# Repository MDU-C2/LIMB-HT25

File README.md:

# LIMB

LIMB is a student project at [Mälardalen University](https://www.mdu.se/) with the aim of creating a bionic arm
to be used in the rehabilitation process of stroke survivors. The arm was
developed in collaboration with [Universidad de Antioquia](http://www.udea.edu.co/),
[Universidad Tecnológica de Panamá](https://utp.ac.pa/), and
[UC Berkeley](https://www.berkeley.edu/).

## Platforms used

The microcontrollers used are ESP32-C3-Zeros and the main computer is an [NVIDIA Jetson AGX Orin Developer Kit](https://www.nvidia.com/en-us/autonomous-machines/embedded-systems/jetson-orin/).

## Controlling the arm

To control the arm first connect to the NVIDIA Jetson AGX Orin. See
the [AGX Orin documentation](/docs/jetson_agx_orin.md) for more details on how to connect to it.
Then you can use CAN messages to control the arm and get information from its sensors.
See the [CAN documentation](/docs/can/can.md) for more details regarding sending and receiving
CAN messages using the AGX Orin. There are various
ready-made python scripts in the [`/src/`](/src/) directory that can be used to control the arm.
See [`/src/README.md`](/src/README.md) for more details on how to run the python scripts.

## Structure of repository

The key parts of the repository are:

- [`scripts/`](./scripts/)
  - Contains a script to set up the virtual CAN interfaces on the Orin.
- [`src/esp32/`](./src/esp32)
  - Contains the programs for the ESP32-C3-Zero modules controlling the motors and reading from the sensors on the robot arm.
- [`src/layers/`](./src/layers)
  - Contains the main program running on the AGX Orin, reading sensor values over the CAN bus from the ESP32s and over Bluetooth Low Energy from the user before figuring out how the robot arm should behave and sending out the new joint angles on the CAN bus to the ESP32s.

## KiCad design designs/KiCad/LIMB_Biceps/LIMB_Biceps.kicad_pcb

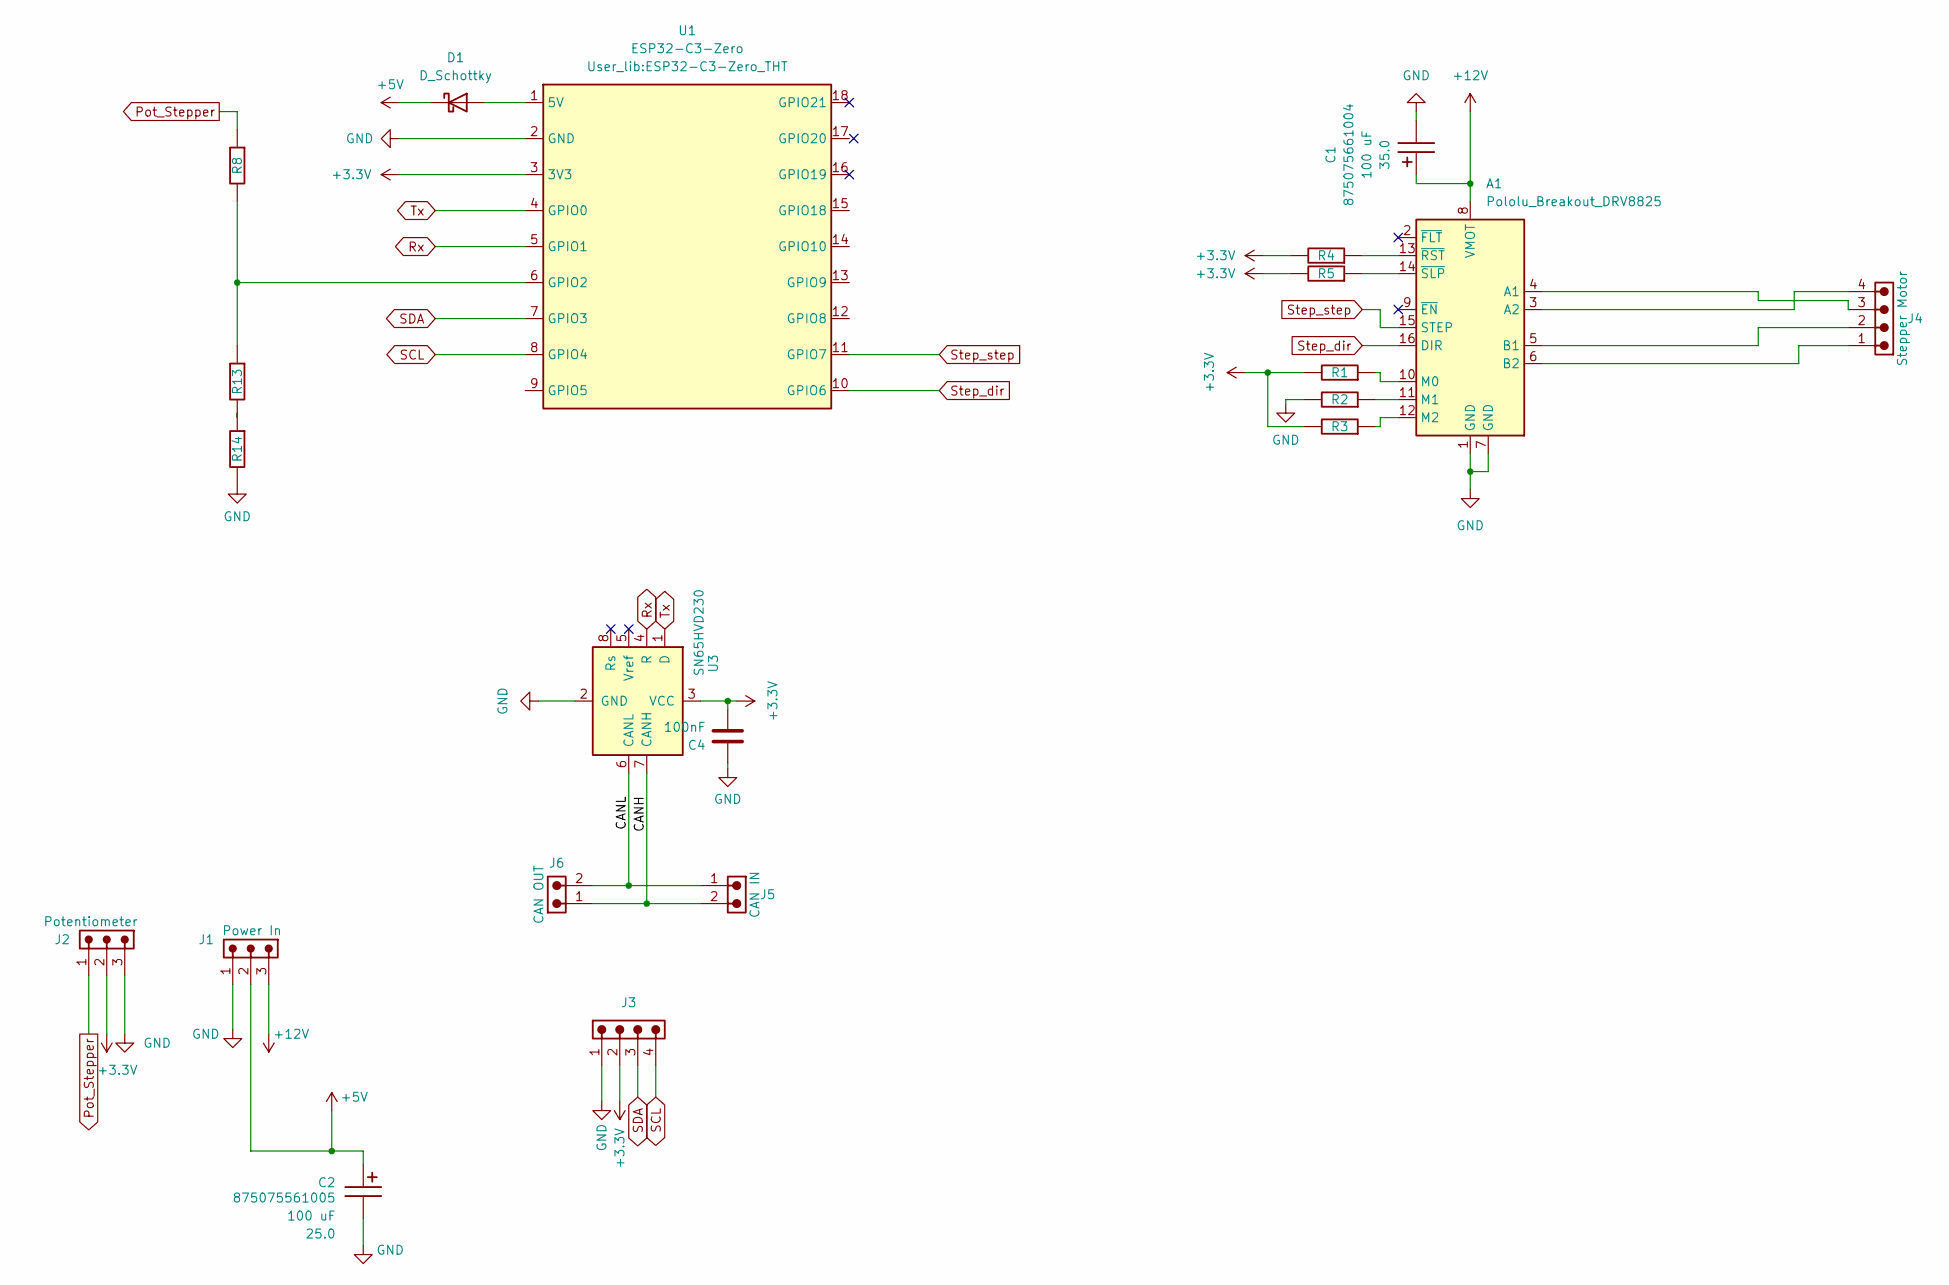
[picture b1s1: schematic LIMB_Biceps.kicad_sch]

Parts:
A1: Pololu_Breakout_DRV8825; Pololu_Breakout-16_15.2x20.3mm
C1: 100 uF; CP_Wurth_WCAP-ASLL-D6.3L5.5; Voltage 35.0; Part Number 875075661004
C2: 100 uF; CP_Wurth_WCAP-ASLL-D6.3L5.5; Voltage 25.0; Part Number 875075561005
C4: 100nF; C_0805_2012Metric_Pad1.18x1.45mm_HandSolder
D1: D_Schottky; D_SMA
J1: Power In; J_Wurth_WR-NPC2_626003110201; Part Number 626003110201
J2: Potentiometer; J_Wurth_WR-NPC2_626003110201; Part Number 626003110201
J3: IMU; J_Wurth_WR-WTB_68800411722; Working Voltage (V (AC)) 250
J4: Stepper Motor; J_Wurth_WR-WTB_68800411722; Working Voltage (V (AC)) 250
J5: CAN IN; J_Wurth_WR-WTB_68800211622; Working Voltage (V (AC)) 250
J6: CAN OUT; J_Wurth_WR-WTB_68800211622; Working Voltage (V (AC)) 250
R1, R2, R3, R4, R5, R8, R13, R14: 10K; R_0805_2012Metric
U1: ESP32-C3-Zero; ESP32-C3-Zero_THT
U3: SN65HVD230; SOIC-8_3.9x4.9mm_P1.27mm

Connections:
+3.3V: C4.2, J2.2, J3.2, R1.1, R3.1, R4.1, R5.1, U1.3 (3V3), U3.3 (VCC)
+5V: C2.1, D1.1 (K), J1.2
+12V: A1.8 (VMOT), C1.1, J1.3
/CANH: J5.2, J6.1, U3.7 (CANH)
/CANL: J5.1, J6.2, U3.6 (CANL)
GND: A1.1 (GND), A1.7 (GND), C1.2, C2.2, C4.1, J1.1, J2.3, J3.1, R2.1, R14.1, U1.2 (GND), U3.2 (GND)
unnamed: A1.4 (A1), J4.3
unnamed: A1.3 (A2), J4.4
unnamed: A1.5 (B1), J4.2
unnamed: A1.6 (B2), J4.1
unnamed: A1.10 (M0), R1.2
unnamed: A1.11 (M1), R2.2
unnamed: A1.12 (M2), R3.2
unnamed: A1.13 (~RST), R4.2
unnamed: A1.14 (~SLP), R5.2
unnamed: D1.2 (A), U1.1 (5V)
unnamed: R13.1, R14.2
unnamed: R8.1, R13.2, U1.6 (GPIO2)
Pot_Stepper: J2.1, R8.2
Rx: U1.5 (GPIO1), U3.4 (R)
SCL: J3.4, U1.8 (GPIO4)
SDA: J3.3, U1.7 (GPIO3)
Step_dir: A1.16 (DIR), U1.10 (GPIO6)
Step_step: A1.15 (STEP), U1.11 (GPIO7)
Tx: U1.4 (GPIO0), U3.1 (D)

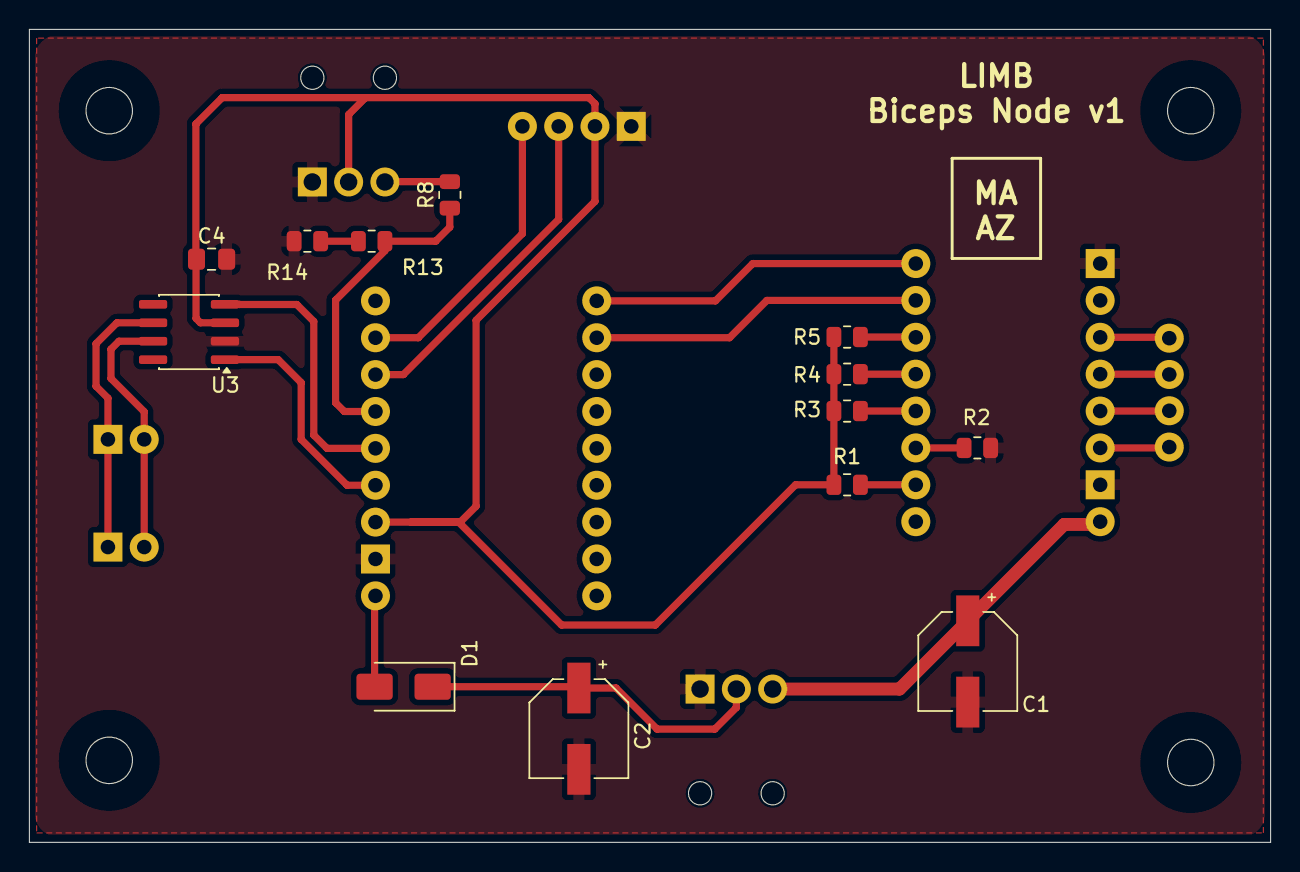
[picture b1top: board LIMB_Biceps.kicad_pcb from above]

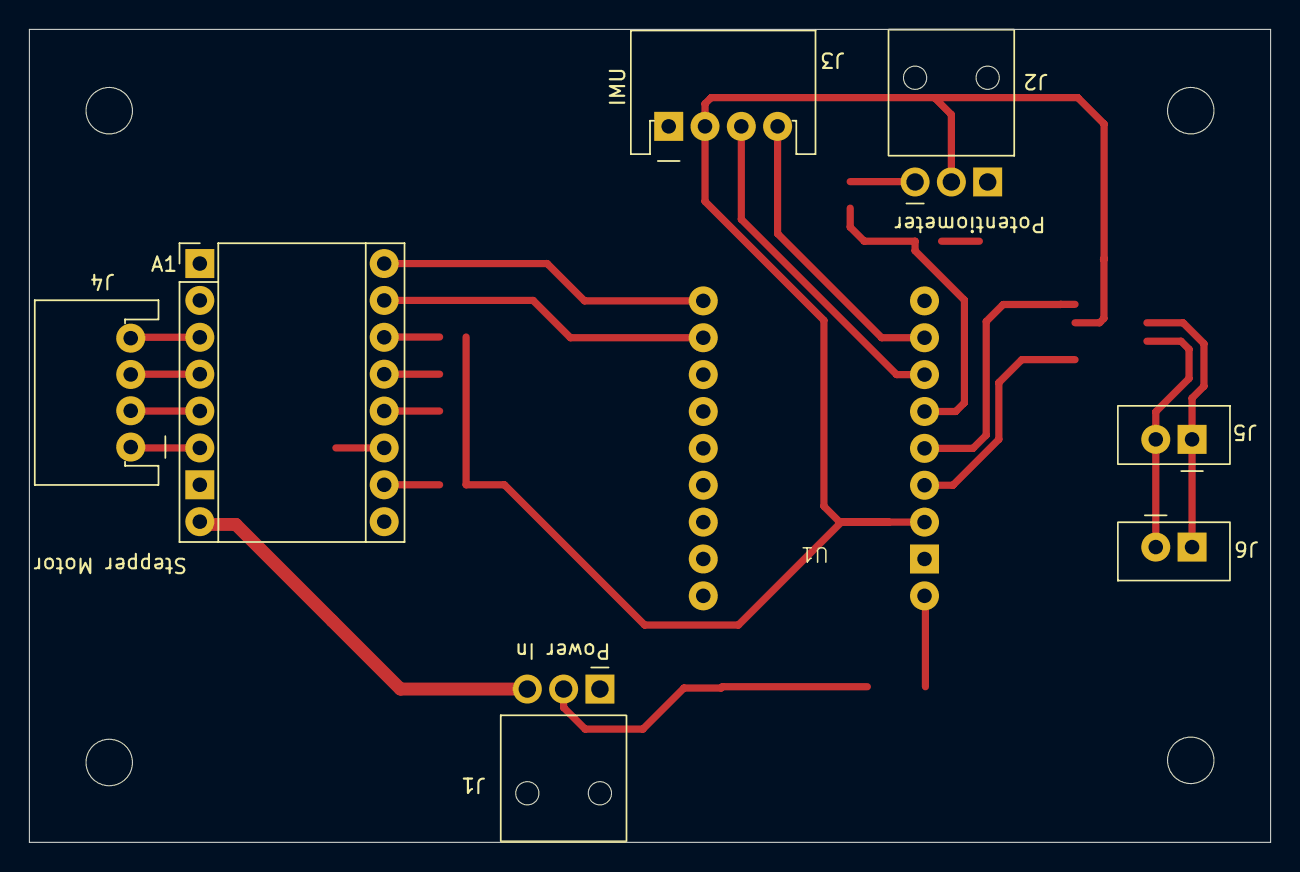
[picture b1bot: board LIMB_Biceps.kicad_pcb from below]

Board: 2 copper layers, 85.5 x 56.0 mm, 21 parts (8 on the bottom side), 25 nets.

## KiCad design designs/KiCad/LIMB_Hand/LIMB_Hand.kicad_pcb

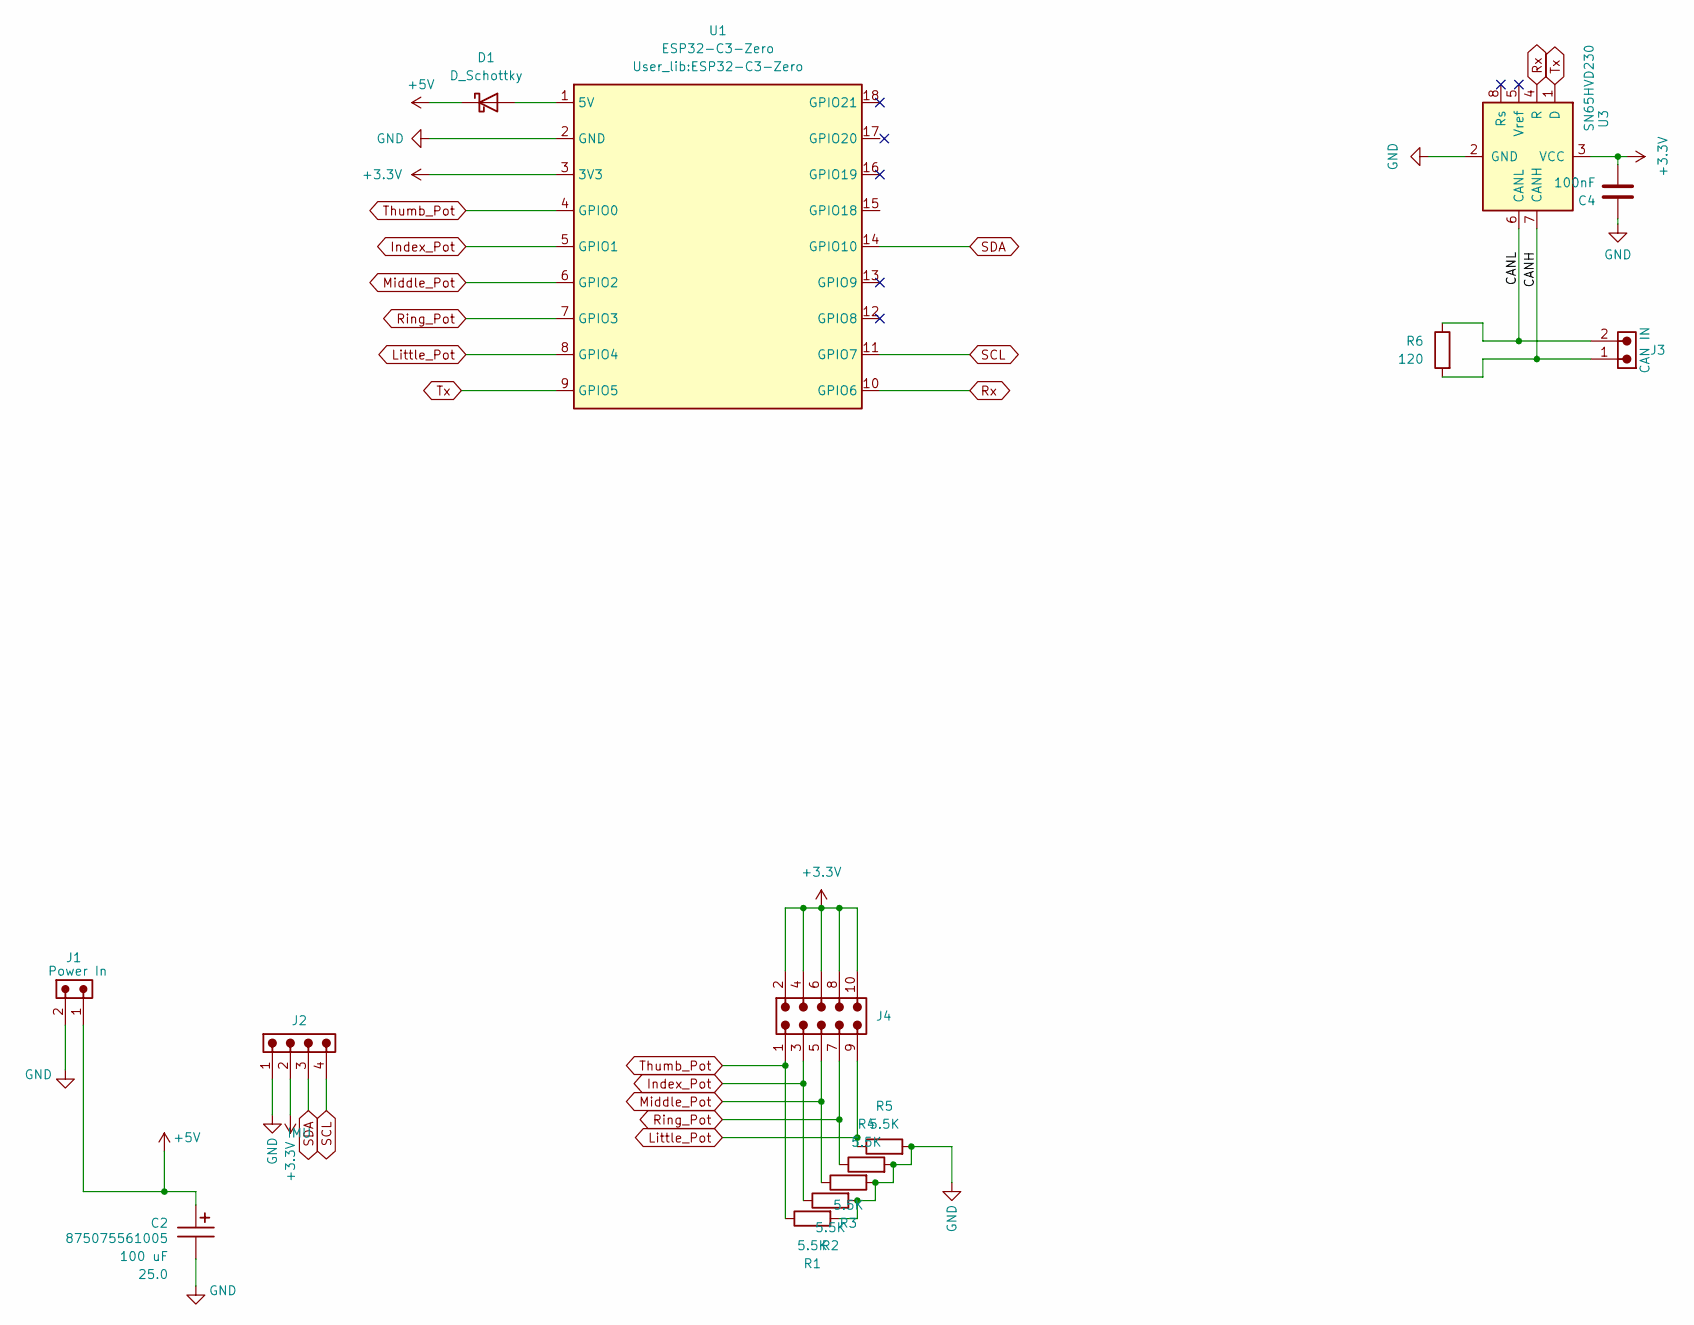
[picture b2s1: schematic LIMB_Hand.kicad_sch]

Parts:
C2: 100 uF; CP_Wurth_WCAP-ASLL-D6.3L5.5; Voltage 25.0; Part Number 875075561005
C4: 100nF; C_0805_2012Metric_Pad1.18x1.45mm_HandSolder
D1: D_Schottky; D_SMA
J1: Power In; J_Wurth_WR-NPC2_626002110201; Part Number 626002110201
J2: IMU; J_Wurth_WR-WTB_68800411622; Working Voltage (V (AC)) 250
J3: CAN IN; J_Wurth_WR-WTB_68800211622; Working Voltage (V (AC)) 250
J4: 61301021121; J_Wurth_WR-PHD_61301021121
R1, R2, R3, R4, R5: 5.5K; R_0805_2012Metric
R6: 120; R_0805_2012Metric
U1: ESP32-C3-Zero
U3: SN65HVD230; SOIC-8_3.9x4.9mm_P1.27mm

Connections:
+3.3V: C4.2, J2.2, J4.2, J4.4, J4.6, J4.8, J4.10, U1.3 (3V3), U3.3 (VCC)
+5V: C2.1, D1.1 (K), J1.1
/CANH: J3.1, R6.2, U3.7 (CANH)
/CANL: J3.2, R6.1, U3.6 (CANL)
GND: C2.2, C4.1, J1.2, J2.1, R1.2, R2.2, R3.2, R4.2, R5.2, U1.2 (GND), U3.2 (GND)
Index_Pot: J4.3, R2.1, U1.5 (GPIO1)
Little_Pot: J4.9, R5.1, U1.8 (GPIO4)
Middle_Pot: J4.5, R3.1, U1.6 (GPIO2)
unnamed: D1.2 (A), U1.1 (5V)
Ring_Pot: J4.7, R4.1, U1.7 (GPIO3)
Rx: U1.10 (GPIO6), U3.4 (R)
SCL: J2.4, U1.11 (GPIO7)
SDA: J2.3, U1.14 (GPIO10)
Thumb_Pot: J4.1, R1.1, U1.4 (GPIO0)
Tx: U1.9 (GPIO5), U3.1 (D)

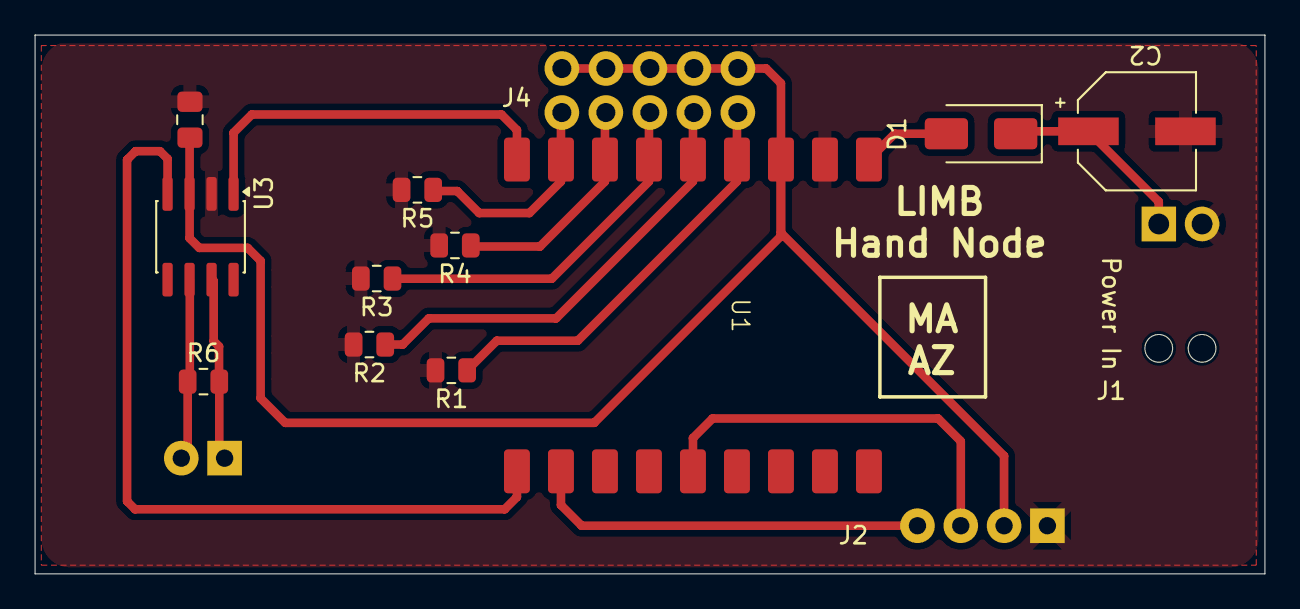
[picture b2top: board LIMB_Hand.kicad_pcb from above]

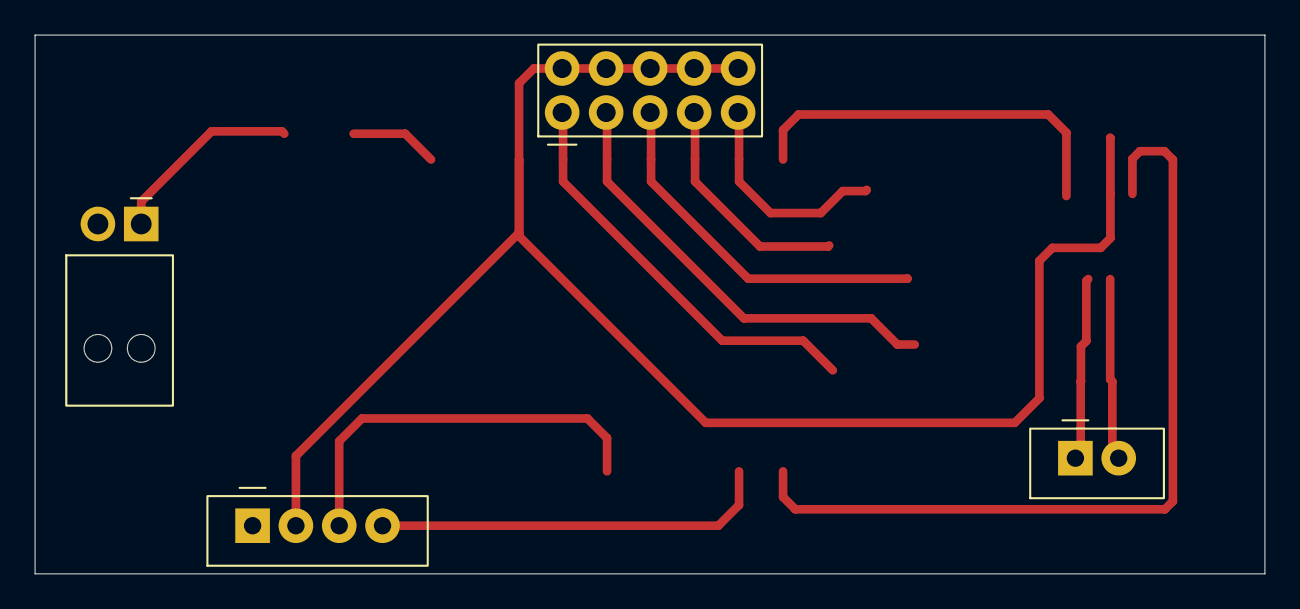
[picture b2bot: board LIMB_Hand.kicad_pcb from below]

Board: 2 copper layers, 71.0 x 31.1 mm, 15 parts (4 on the bottom side), 15 nets.

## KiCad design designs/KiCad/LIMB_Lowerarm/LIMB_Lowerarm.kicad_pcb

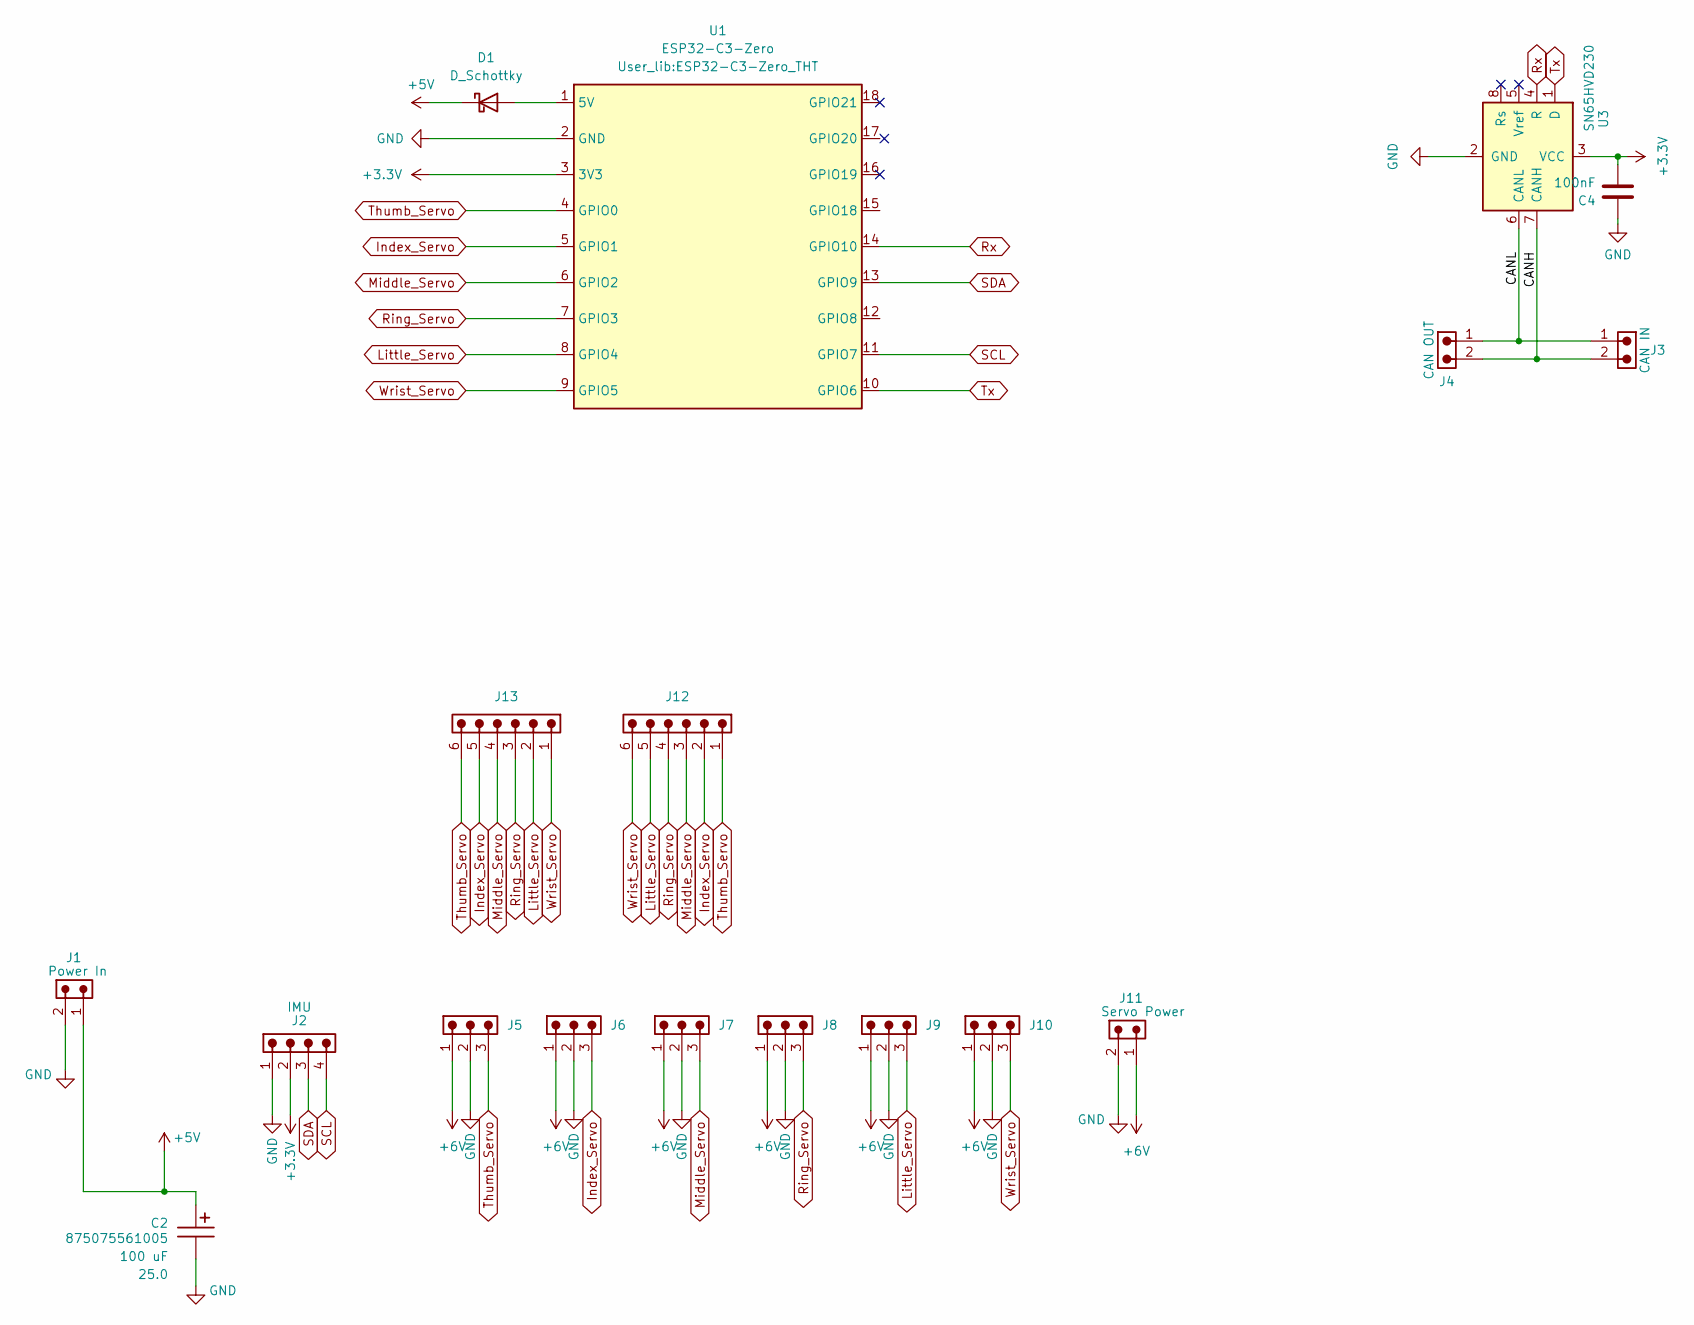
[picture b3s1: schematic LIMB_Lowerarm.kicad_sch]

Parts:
C2: 100 uF; CP_Wurth_WCAP-ASLL-D6.3L5.5; Voltage 25.0; Part Number 875075561005
C4: 100nF; C_0805_2012Metric_Pad1.18x1.45mm_HandSolder
D1: D_Schottky; D_SMA
J1: Power In; J_Wurth_WR-NPC2_626002110201; Part Number 626002110201
J2: IMU; J_Wurth_WR-WTB_68800411622; Working Voltage (V (AC)) 250
J3: CAN IN; J_Wurth_WR-WTB_68800211622; Working Voltage (V (AC)) 250
J4: CAN OUT; J_Wurth_WR-WTB_68800211622; Working Voltage (V (AC)) 250
J5, J6, J7, J8, J9, J10: 68800311622; J_Wurth_WR-WTB_68800311622; Working Voltage (V (AC)) 250
J11: Servo Power; J_Wurth_WR-NPC2_626002110201; Part Number 626002110201
J12, J13: 68800611722; J_Wurth_WR-WTB_68800611722; Working Voltage (V (AC)) 250
U1: ESP32-C3-Zero; ESP32-C3-Zero_THT
U3: SN65HVD230; SOIC-8_3.9x4.9mm_P1.27mm

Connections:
+3.3V: C4.2, J2.2, U1.3 (3V3), U3.3 (VCC)
+5V: C2.1, D1.1 (K), J1.1
+6V: J5.1, J6.1, J7.1, J8.1, J9.1, J10.1, J11.1
/CANH: J3.2, J4.2, U3.7 (CANH)
/CANL: J3.1, J4.1, U3.6 (CANL)
GND: C2.2, C4.1, J1.2, J2.1, J5.2, J6.2, J7.2, J8.2, J9.2, J10.2, J11.2, U1.2 (GND), U3.2 (GND)
Index_Servo: J6.3, J12.2, J13.5, U1.5 (GPIO1)
Little_Servo: J9.3, J12.5, J13.2, U1.8 (GPIO4)
Middle_Servo: J7.3, J12.3, J13.4, U1.6 (GPIO2)
unnamed: D1.2 (A), U1.1 (5V)
Ring_Servo: J8.3, J12.4, J13.3, U1.7 (GPIO3)
Rx: U1.14 (GPIO10), U3.4 (R)
SCL: J2.4, U1.11 (GPIO7)
SDA: J2.3, U1.13 (GPIO9)
Thumb_Servo: J5.3, J12.1, J13.6, U1.4 (GPIO0)
Tx: U1.10 (GPIO6), U3.1 (D)
Wrist_Servo: J10.3, J12.6, J13.1, U1.9 (GPIO5)

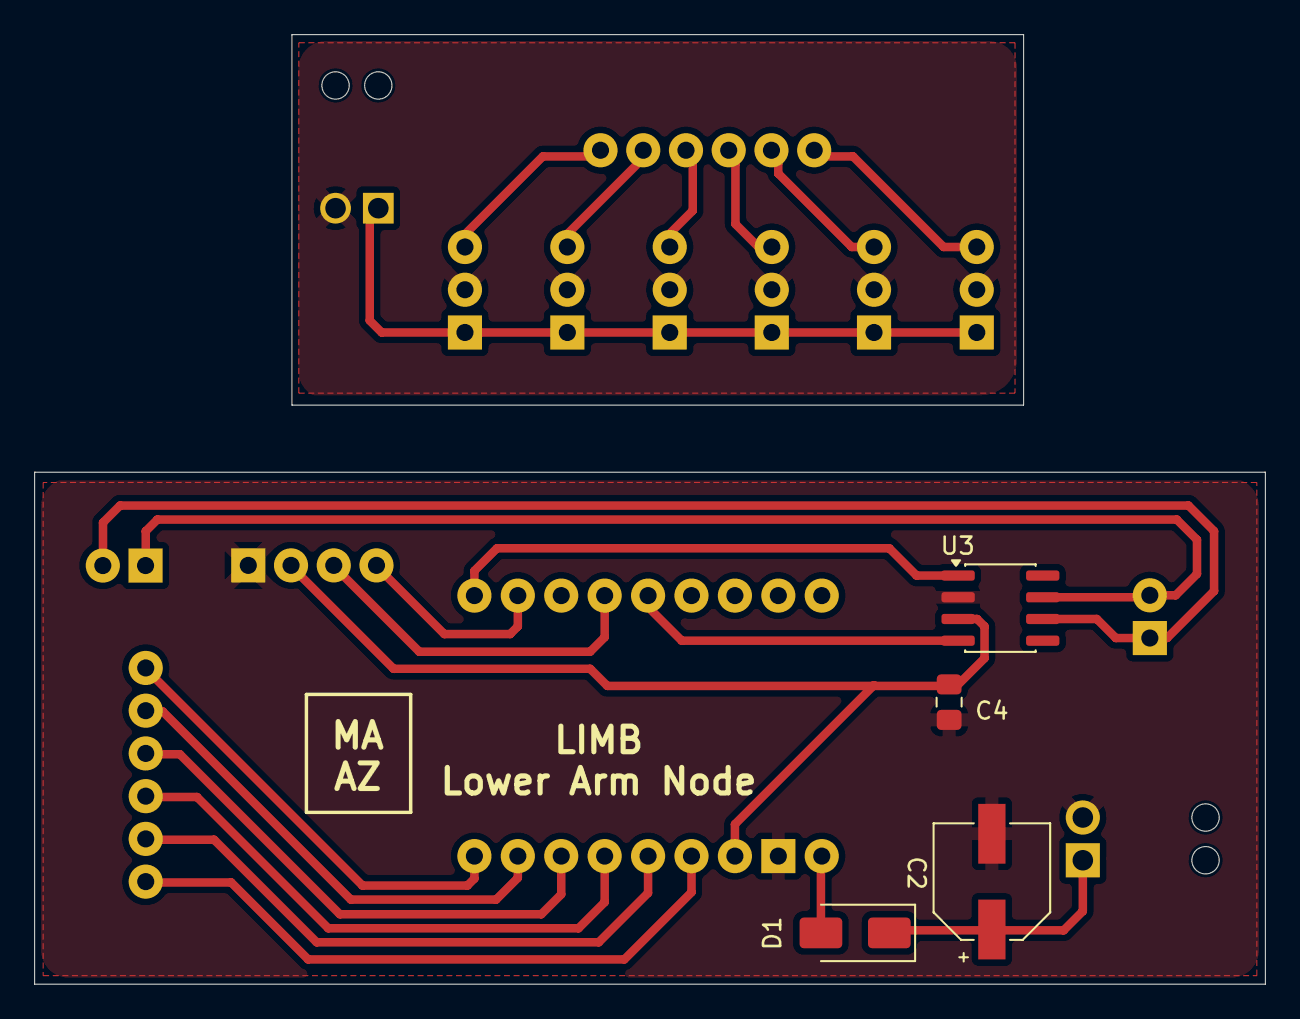
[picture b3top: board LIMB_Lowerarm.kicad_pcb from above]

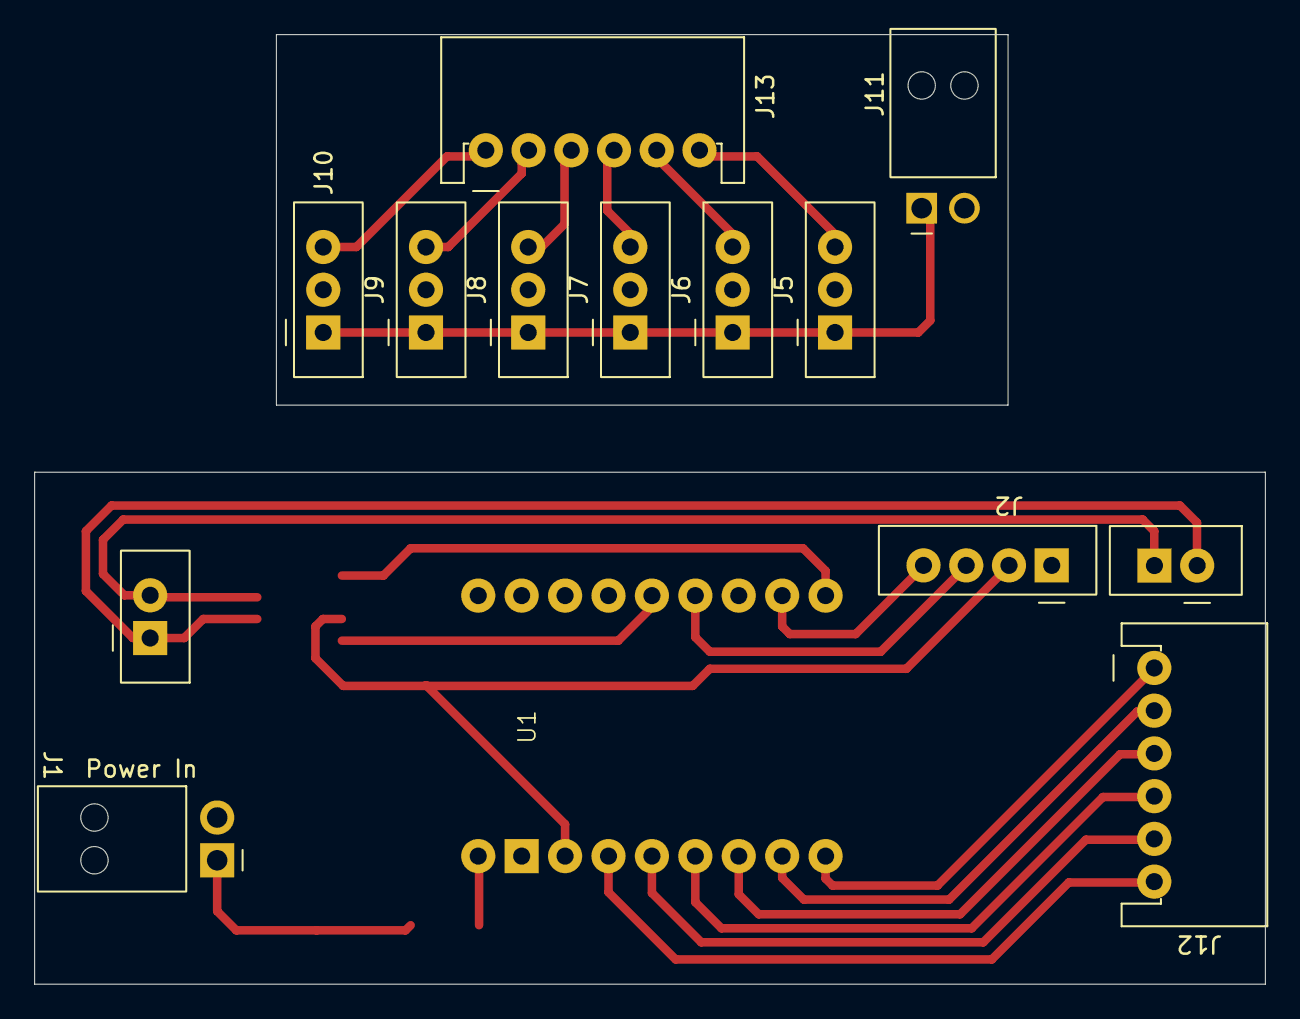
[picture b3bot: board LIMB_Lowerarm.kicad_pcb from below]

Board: 2 copper layers, 72.0 x 55.5 mm, 18 parts (14 on the bottom side), 17 nets.

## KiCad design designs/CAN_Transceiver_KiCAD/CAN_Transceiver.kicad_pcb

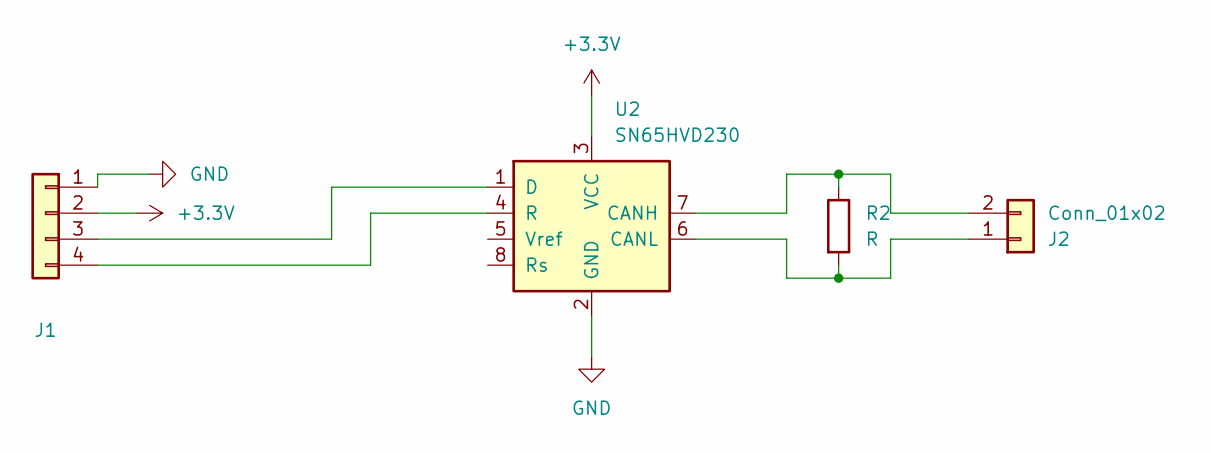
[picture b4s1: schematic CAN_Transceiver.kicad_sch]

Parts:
J1: Conn_01x04; PinHeader_1x04_P2.54mm_Vertical
J2: Conn_01x02; PinHeader_1x02_P2.54mm_Vertical
R2: R; R_0603_1608Metric_Pad0.98x0.95mm_HandSolder
U2: SN65HVD230; SOIC-8_3.9x4.9mm_P1.27mm

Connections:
+3.3V: J1.2, U2.3 (VCC)
GND: J1.1, U2.2 (GND)
unnamed: J1.3, U2.1 (D)
unnamed: J1.4, U2.4 (R)
unnamed: J2.1, R2.2, U2.6 (CANL)
unnamed: J2.2, R2.1, U2.7 (CANH)

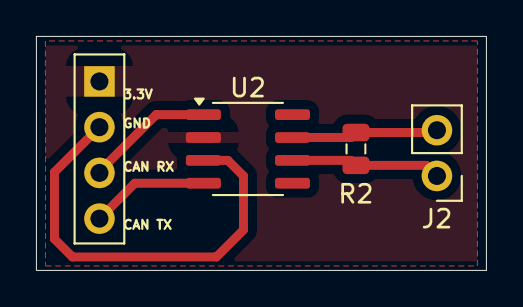
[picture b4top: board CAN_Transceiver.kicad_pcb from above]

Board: 2 copper layers, 25.0 x 13.0 mm, 4 parts (0 on the bottom side), 6 nets.

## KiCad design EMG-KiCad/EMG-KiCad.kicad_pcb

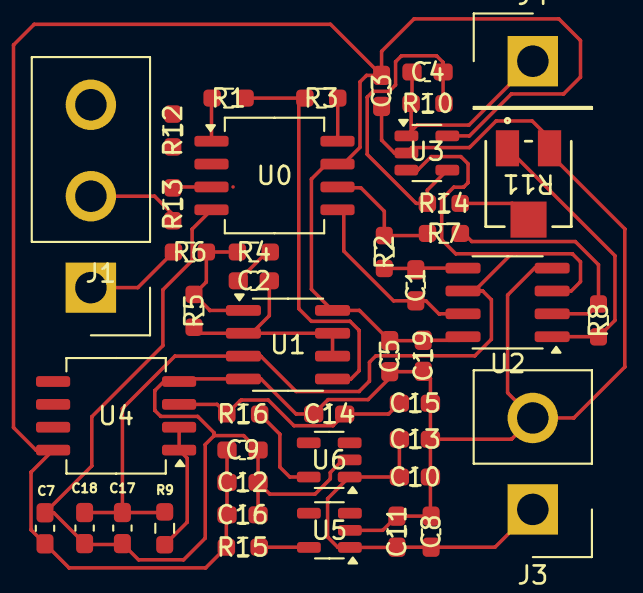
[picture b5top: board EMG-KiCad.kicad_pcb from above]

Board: 2 copper layers, 44 parts (0 on the bottom side), 27 nets.

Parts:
C1, C2, C3, C4, C5, C7, C8, C9, C10, C11, C12, C13, C14, C15, C16, C17, C18, C19: C_Small; C_0603_1608Metric_Pad1.08x0.95mm_HandSolder
J1: Conn_01x03_Socket; Samtec_HPM-03-05-x-S_Straight_1x03_Pitch5.08mm
J3: Conn_01x02_Socket; Samtec_HPM-02-05-x-S_Straight_1x02_Pitch5.08mm
J4: Conn_01x01_Socket; Samtec_HPM-01-05-x-S_Straight_1x01_Pitch5.08mm
R1, R2, R3, R4, R5, R6, R7, R8, R9, R10, R12, R13, R14, R15, R16: R_Small; R_0603_1608Metric_Pad0.98x0.95mm_HandSolder
R11: 3314J-1-103E; POT_3314J
U0: AD623; SOIC-8_5.3x6.2mm_P1.27mm
U1, U2: OPA2333xxD; SOIC-8_3.9x4.9mm_P1.27mm
U3: OPA333xxDBV; SOT-23-5
U4: OPA350UA; SOIC-8_5.3x6.2mm_P1.27mm
U5: LDO 3.3; SOT-23-5
U6: LDO 1.5; SOT-23-5

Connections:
/V+: C3.2, C5.1, C7.1, C9.1, C12.1, C16.2, C19.2, R15.2, U0.7 (Vs+), U1.8 (V+), U2.8 (V+), U3.5 (V+), U4.8 (V+)
/Vout: C4.2, J4.1, R10.2, U3.1
/Vpower: C8.1, C10.1, C11.1, C13.1, J3.1, U5.1 (IN), U6.1 (IN)
/Vref: C17.1, C18.1, R9.1, U1.3 (+), U2.3 (+), U2.6 (-), U3.3 (+)
Earth: C3.1, C5.2, C7.2, C8.2, C9.2, C10.2, C11.2, C12.2, C13.2, C14.2, C15.2, C16.1, C17.2, C18.2, C19.1, J3.2, R11.3, U0.4 (Vs-), U1.4 (V-), U2.4 (V-), U3.2 (V-), U4.4 (V-), U5.2 (GND), U6.2 (GND)
unnamed: C2.1, R4.2
unnamed: J1.1, R6.1
unnamed: J1.2, R13.1
unnamed: J1.3, R12.1
unnamed: R1.1, U0.1 (Rg)
unnamed: R2.2, R7.1, U0.6
unnamed: R3.1, U0.8 (Rg)
unnamed: R4.1, R5.1, R6.2, U1.1
unnamed: R8.1, R11.1, U2.1
unnamed: R11.2, R14.2
unnamed: R13.2, U0.3 (+)
unnamed: R12.2, U0.2 (-)
unnamed: C1.1, U0.5 (Ref), U2.7
unnamed: C2.2, R5.2, U1.2 (-), U1.6 (-), U1.7
unnamed: R1.2, R3.2, U1.5 (+)
unnamed: R7.2, R8.2, U2.2 (-)
unnamed: C1.2, R2.1, U2.5 (+)
unnamed: C4.1, R10.1, R14.1, U3.4 (-)
unnamed: C14.1, C15.1, R16.2, U4.3 (+)
unnamed: R9.2, U4.1, U4.2 (-)
unnamed: R15.1, U5.5 (OUT)
unnamed: R16.1, U6.5 (OUT)

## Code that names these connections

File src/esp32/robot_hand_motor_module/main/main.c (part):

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  PINKY_CONFIG_INDEX = 4,
  WRIST_CONFIG_INDEX = 5,

  THUMB_SERVO_GPIO = GPIO_NUM_0,
  INDEX_SERVO_GPIO = GPIO_NUM_1,
  MID_SERVO_GPIO = GPIO_NUM_2,
  RING_SERVO_GPIO = GPIO_NUM_3,
  PINKY_SERVO_GPIO = GPIO_NUM_4,
  TWIST_SERVO_GPIO = GPIO_NUM_5,
};
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// Servo configurations - customize each servo individually
static const servo_config_t s_servo_configs[] = {
    // Thumb servo
    [THUMB_CONFIG_INDEX] = {.gpio_pin = THUMB_SERVO_GPIO,
                            .ledc_channel = LEDC_CHANNEL_0,
                            .max_angle = 30,
                            .min_angle = 0,
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                            .direction = SERVO_DIR_REVERSE,
                            .name = "Thumb"},
    // Index finger
    [INDEX_CONFIG_INDEX] = {.gpio_pin = INDEX_SERVO_GPIO,
                            .ledc_channel = LEDC_CHANNEL_1,
                            .max_angle = 85,
                            .min_angle = 0,
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                             .direction = SERVO_DIR_REVERSE,
                             .name = "Middle"},
    // Ring finger
    [RING_CONFIG_INDEX] = {.gpio_pin = RING_SERVO_GPIO,
                           .ledc_channel = LEDC_CHANNEL_3,
                           .max_angle = 50,
                           .min_angle = 0,
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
